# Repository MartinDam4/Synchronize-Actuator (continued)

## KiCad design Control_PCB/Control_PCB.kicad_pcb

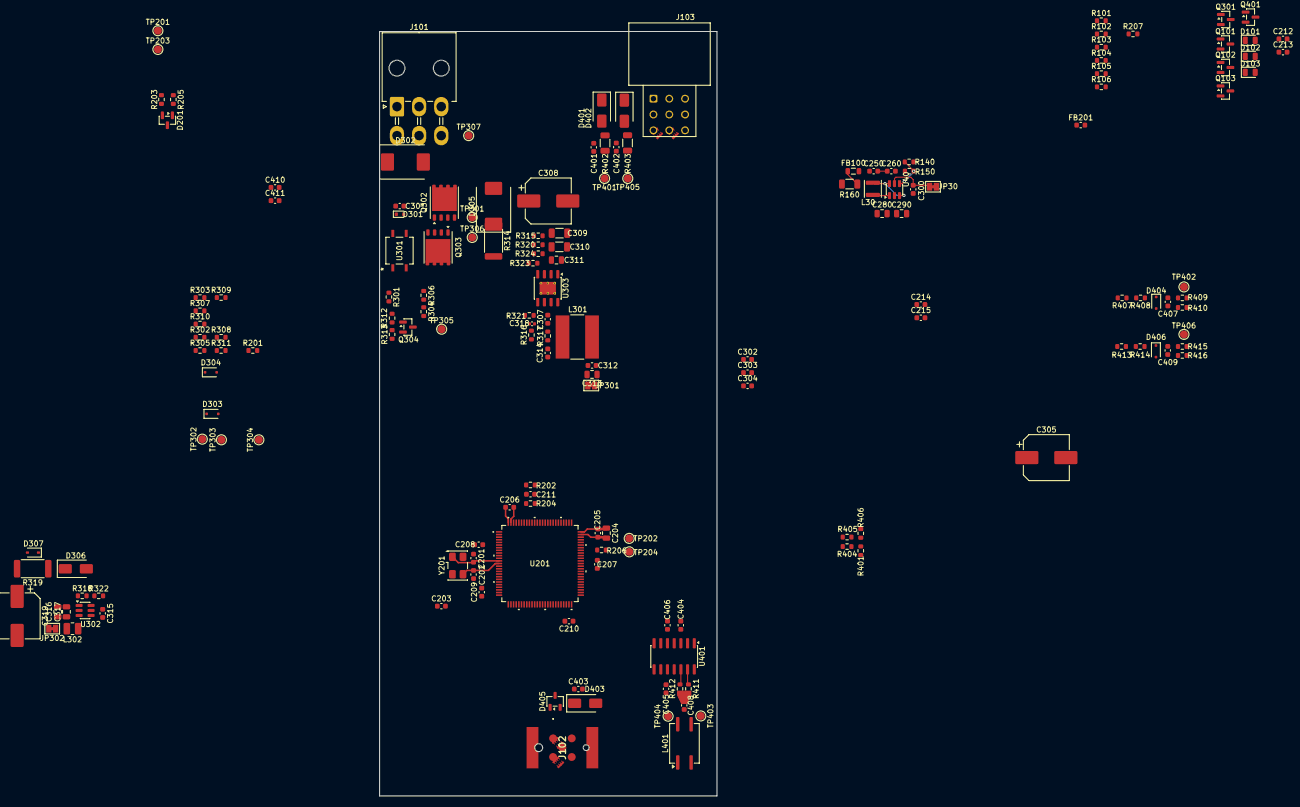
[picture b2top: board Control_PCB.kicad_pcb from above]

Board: 4 copper layers, 64.0 x 145.0 mm, 171 parts (1 on the bottom side), 87 nets.

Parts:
C201, C202: 24p; C_0603_1608Metric
C203, C301: 10n; C_0603_1608Metric
C204, C313, C316, C317: 22u; C_0805_2012Metric
C205, C206, C207, C208, C209, C210, C212, C214, C260, C312, C401, C402, C403, C404, C405, C406: 100n; C_0603_1608Metric
C211, C213, C215, C250, C315: 1u; C_0603_1608Metric
C280, C290: 2.2u; C_0805_2012Metric
C300: 10u; C_0603_1608Metric
C302, C303, C304, C410, C411: 47n; C_0603_1608Metric
C305, C308: 47u; CP_Elec_8x10.5
C307: 2.2n; C_0603_1608Metric
C309, C310: 2.2u; C_1206_3216Metric
C311: 100n; C_0805_2012Metric
C314: 1.2n; C_0603_1608Metric
C318: 56p; C_0402_1005Metric
C319: 1.5m; CP_Elec_8x10.5
C407, C409: 1n; C_0603_1608Metric
C408: 4.7n; C_0603_1608Metric
D101: RED; LED_0805_2012Metric
D102: Green; LED_0805_2012Metric
D103: White; LED_0805_2012Metric
D201: PESD5V2S2UT; SOT-23
D301: MM5Z12V; D_SOD-523
D302: SMDJ58CA; D_SMC
D303, D304: MM3Z56VB; D_SOD-323F
D305: S3M-13-F; D_SMC
D306: B360A; D_SMA
D307: 1N5819WS; D_SOD-323
D401, D402: SMAJ58A; D_SMA
D403: SMAJ16A; D_SMA
D404, D406: MM3Z62VB; D_SOD-323F
D405: ESD2CANFD60-Q1; SOT-23-3
E401, E402, E403, E404: SparkGap; Sparkgap_2021-09-02
FB100: FerriteBead_Small; L_0805_2012Metric
FB201: FerriteBead_Small; L_0603_1608Metric
J101: Minifit 2x3; Molex_Mini-Fit_Jr_5569-06A2_2x03_P4.20mm_Horizontal
J102: Conn_01x05; 1411976
J103: Conn_01x09; Molex_Micro-Fit_3x03_P3.00mm
J201: Micro Match; CONN6_7-188275-6_TEC
JP30, JP301, JP302: SolderJumper; SolderJumper-2_P1.3mm_Bridged_Pad1.0x1.5mm
L30: 10u; L_APV_ANR3012
L301: 100u; L_Bourns-SRN8040_8x8.15mm
L302: 1u; L_1008_2520Metric
L401: DR331-513AE; L_CommonMode_Bourns_DR331
Q101, Q102, Q103, Q301, Q401: MMBT3904; SOT-23
Q302, Q303: TPH4R50ANH1; Infineon_PG-TDSON-8_6.15x5.15mm
Q304: 2N7002; SOT-23
R101: 270; R_0603_1608Metric
R102, R103, R203, R205: 120; R_0603_1608Metric
R104, R105, R106, R201, R304, R405: 10k; R_0603_1608Metric
R140: 0; R_0603_1608Metric
R150: 47k; R_0603_1608Metric
R160: 1; R_1206_3216Metric
R202: 15k; R_0603_1608Metric
R204, R302, R303, R306, R313, R318, R406, R409, R415: 100k; R_0603_1608Metric
R206, R315, R320: 470k; R_0603_1608Metric
R207: 47; R_0603_1608Metric
R301: 200; R_0603_1608Metric
R305, R307, R308: 220k; R_0603_1608Metric
R309, R310: 12k; R_0603_1608Metric
R311: 68k; R_0603_1608Metric
R312: 1Meg; R_0603_1608Metric
R314: 47R - 3W; R_2512_6332Metric
R316: 390k; R_0603_1608Metric
R317, R324: 240k; R_0603_1608Metric
R319: 5.6; R_2512_6332Metric
R321: 120k; R_0603_1608Metric
R322: 22k; R_0603_1608Metric
R323: 39k; R_0603_1608Metric
R401: 1k; R_0603_1608Metric
R402, R403: 100; R_1206_3216Metric
R404: 100; R_0603_1608Metric
R407, R408, R413, R414: 18k; R_0603_1608Metric
R410, R416: 4k7; R_0603_1608Metric
R411, R412: 60; R_0603_1608Metric
TP201, TP202, TP203, TP204, TP301, TP302, TP303, TP304, TP305, TP306, TP307, TP401, TP402, TP403, TP404, TP405, TP406: TestPoint; TestPoint_Pad_D1.5mm
U40: TLV61046ADB; SOT-23-6
U201: STM32G473VET3; LQFP100-14x14mm
U301: VOM1271T; SOP-4_VIS
U302: TPS62A01APDDC; SOT-23-6
U303: LM5164DDA; HSOP-8-1EP_3.9x4.9mm_P1.27mm_EP2.41x3.1mm_ThermalVias
U401: TCAN1043xDxQ1; SOIC-14_3.9x8.7mm_P1.27mm
Y201: ABM3BAIG; Crystal_SMD_5032-4Pin_5.0x3.2mm

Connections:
+3V3: C204.1, C205.1, C206.1, C207.1, C208.1, C209.1, C210.1, C406.1, FB201.2, J201.5, JP302.2 (B), R201.2, U201.6 (VBAT), U201.24 (VDD), U201.49 (VDD), U201.64 (VDD), U201.75 (VDD), U201.100 (VDD), U301.1, U401.5 (VIO)
+3V3_VDDA: C212.1, C213.1, FB201.1, R207.1, U201.37 (VDDA)
+5V: C404.1, C405.1, D101.2 (A), D102.2 (A), D103.2 (A), D306.2 (A), JP301.2 (B), R160.1, R308.1, R401.2, U401.3 (VCC), U401.10 (VSUP)
/IO_Interface/AD_GPIO1: C410.1, R409.2, R410.2, TP402.1 (1_1), U201.22 (PA2)
/IO_Interface/AD_GPIO2: C411.1, R415.2, R416.2, TP406.1 (1_1), U201.25 (PA3)
/IO_Interface/CANH: D405.1 (A1), E404.2, J102.4, L401.2
/IO_Interface/CANL: D405.2 (A2), E403.2, J102.5, L401.1
/IO_Interface/CAN_ENA: U201.96 (PB9), U401.6 (EN)
/IO_Interface/CAN_FAULT: U201.9 (PC15-OSC32_OUT), U401.8 (~FAULT)
/IO_Interface/CAN_RX: U201.72 (PA11), U401.4 (RXD)
/IO_Interface/CAN_STB: U201.61 (PD14), U401.14 (~STB)
/IO_Interface/CAN_TX: U201.73 (PA12), U401.1 (TXD)
/IO_Interface/GPIO1: D401.1 (A1), E401.2, J103.7, R402.2
/IO_Interface/GPIO2: D402.1 (A1), E402.2, J103.8, R403.2
/IO_Interface/GPIO_1: C401.1, R402.1, R407.1, TP401.1 (1_1)
/IO_Interface/GPIO_2: C402.1, R403.1, R413.1, TP405.1 (1_1)
/IO_Interface/HEARTBEAT: C403.1, D403.1 (A1), J102.2, R404.2
/IO_Interface/HEARTBEAT_mcu: R405.2, U201.92 (PB5)
/Power/AD_VCC: C303.1, R307.2, R310.1, TP303.1 (1_1), U201.31 (PC5)
/Power/AD_VCC_IN: C302.1, R305.2, R309.1, TP302.1 (1_1), U201.21 (PA1)
/Power/ENA_INRUSH: R304.1, U201.89 (PD7)
/Power/PGOOD: R140.1, U303.6 (PGOOD)
/mcu/AD_5V: C304.1, R308.2, R311.1, TP304.1 (1_1), U201.33 (PB1)
/mcu/LED_BLUE: R106.2, U201.58 (PD11)
/mcu/LED_GREEN: R105.2, U201.46 (PE15)
/mcu/LED_RED: R104.2, U201.68 (PC9)
/mcu/PROG_BOOT: C211.2, R202.2, R204.2, U201.95 (PB8-BOOT0)
/mcu/PROG_RX: D201.2 (K), R202.1, R203.2, TP202.1 (1_1), U201.71 (PA10)
/mcu/PROG_TX: D201.1 (K), R205.2, R206.2, TP204.1 (1_1), U201.70 (PA9)
/mcu/SWD_CLK: J201.3, U201.77 (PA14)
/mcu/SWD_IO: J201.1, U201.76 (PA13)
/mcu/SWO: J201.6, U201.90 (PB3)
/mcu/~RST: C203.2, J201.4, R201.1, U201.14 (PG10-NRST)
GND: C201.2, C202.2, C203.1, C204.2, C205.2, C206.2, C207.2, C208.2, C209.2, C210.2, C211.1, C212.2, C213.2, C214.2, C215.2, C250.2, C260.2, C280.2, C290.2, C300.2, C302.2, C303.2, C304.2, C305.2, C308.2, C309.2, C310.2, C311.2, C312.2, C313.2, C315.2, C316.2, C317.2, C319.2, C401.2, C402.2, C403.2, C404.2, C405.2, C406.2, C407.1, C408.2, C409.1, C410.2, C411.2, D201.3 (A), D302.1 (A1), D303.2 (A), D304.2 (A), D401.2 (A2), D402.2 (A2), D403.2 (A2), D404.2 (A), D405.3 (common), D406.2 (A), E401.1, E402.1, E403.1, E404.1, J101.1, J101.2, J101.3, J102.1, J102.3, J103.3, J201.2, Q101.2 (E), Q102.2 (E), Q103.2 (E), Q304.2 (S), Q401.2 (E), R204.1, R206.1, R306.2, R309.2, R310.2, R311.2, R313.1, R321.2, R322.2, R323.2, R324.2, R406.1, R410.1, R416.1, U40.2 (GND), U201.23 (VSS), U201.35 (VSSA), U201.48 (VSS), U201.63 (VSS), U201.74 (VSS), U201.99 (VSS), U302.2 (GND), U302.5 (PG), U303.1 (GND), U303.9 (EP), U401.2 (GND), U401.9 (WAKE), Y201.2 (G), Y201.4 (G)
unnamed: C314.1, C318.2, R317.2
unnamed: C408.1, R411.2, R412.1
unnamed: D101.1 (K), R101.2
unnamed: D102.1 (K), R102.2
unnamed: D103.1 (K), R103.2
unnamed: C301.2, D301.2 (A), Q302.1 (S), Q302.2 (S), Q302.3 (S), Q303.1 (S), Q303.2 (S), Q303.3 (S), TP306.1 (1_1), U301.3
unnamed: C301.1, D301.1 (K), Q302.4 (G), Q303.4 (G), TP301.1 (1_1), U301.4
unnamed: D303.1 (K), R302.2, R305.1
unnamed: D304.1 (K), R303.2, R307.1
unnamed: D305.1 (K), R314.1
unnamed: C315.1, D306.1 (K), D307.1 (K), R319.1, U302.1 (EN), U302.4 (VIN)
unnamed: C319.1, D307.2 (A), R319.2
unnamed: C407.2, D404.1 (K), R408.2, R409.1
unnamed: C409.2, D406.1 (K), R414.2, R415.1
unnamed: FB100.1, R160.2
unnamed: C300.1, JP30.1 (A), U40.5 (VOUT)
unnamed: C312.1, C313.1, C314.2, JP301.1 (A), L301.2, R316.1
unnamed: C316.1, C317.1, JP302.1 (A), L302.2, R318.1
unnamed: Q101.1 (B), R104.1
unnamed: Q101.3 (C), R101.1
unnamed: Q102.1 (B), R105.1
unnamed: Q102.3 (C), R102.1
unnamed: Q103.1 (B), R106.1
unnamed: Q103.3 (C), R103.1
unnamed: Q301.1 (B), R304.2, R306.1
unnamed: Q301.3 (C), R301.2
unnamed: Q301.2 (E), Q304.3 (D)
unnamed: Q304.1 (G), R312.2, R313.2
unnamed: Q401.1 (B), R405.1, R406.2
unnamed: Q401.3 (C), R401.1, R404.1
unnamed: R203.1, TP201.1 (1_1)
unnamed: R205.1, TP203.1 (1_1)
unnamed: R301.1, U301.2
unnamed: R315.2, R320.1
unnamed: R407.2, R408.1
unnamed: R413.2, R414.1
unnamed: C280.1, C290.1, R140.2, R150.2, U40.4 (EN)
unnamed: C250.1, C260.1, FB100.2, L30.1, R150.1, U40.3 (FB), U40.6 (VI)
unnamed: L30.2, U40.1 (SW)
unnamed: C201.1, U201.12 (PF0-OSC_IN), Y201.1
unnamed: C202.1, U201.13 (PF1-OSC_OUT), Y201.3
unnamed: C214.1, C215.1, R207.2, U201.36 (VREF+)
unnamed: R318.2, R322.1, U302.6 (FB)
unnamed: L302.1, U302.3 (SW)
unnamed: C307.2, U303.7 (BST)
unnamed: R320.2, R324.1, U303.3 (EN/UVLO)
unnamed: C318.1, R316.2, R321.1, U303.5 (FB)
unnamed: R323.1, U303.4 (RON)
unnamed: C307.1, L301.1, R317.1, U303.8 (SW)
unnamed: L401.3, R411.1, TP403.1 (1_1), U401.13 (CANH)
unnamed: L401.4, R412.2, TP404.1 (1_1), U401.12 (CANL)
VCC: C305.1, C308.1, C309.1, C310.1, C311.1, Q303.5 (D), R303.1, R314.2, R315.1, TP305.1 (1_1), U303.2 (VIN)
VCC_IN: D302.2 (A2), D305.2 (A), J101.4, J101.5, J101.6, Q302.5 (D), R302.1, R312.1, TP307.1 (1_1)
